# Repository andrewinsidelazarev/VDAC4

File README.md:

# VDAC4

Плата VDAC4 для ZX Evolution (TS-Config): Tang Nano 20K, модуль Waveshare
ESP32-S3-Zero-N8R8 и ЦАП PCM5102. ESP32-S3 подключена к Evo по SPI — к той же
шине, что и SD-карта (порты `#57`/`#77`), и работает ведомой: Z80 обращается к ней
двоичным протоколом ZiFi. Сеть, разбор HTTP, файловые серверы и декодирование
звука делает ESP; программы Z80 — плагины Wild Commander и `zifi.spg` —
показывают интерфейс и работают с картой Evo.

## Первая прошивка платы — готовая программа

> [!TIP]
> **Прошить новую плату или поставить прошивки заново можно готовой программой — собирать ничего не нужно.**
>
> **[⬇ Скачать VDAC4Flasher.exe](https://github.com/andrewinsidelazarev/VDAC4/raw/main/Flasher/VDAC4Flasher.exe)** — одна программа для Windows 10/11.
>
> Она сама скачивает свежие прошивки отсюда, с GitHub, и по шагам записывает их по USB во все три части платы:
> модуль ESP32-S3 Zero, BL616 модуля Tang Nano 20K и flash ПЛИС Tang. Перед записью старые прошивки сохраняются
> в папку `Backup` рядом с программой. Python, ESP-IDF, Gowin и другие программы не нужны.

Как пользоваться:

1. Создайте пустую папку (например, `VDAC4` на рабочем столе) и скачайте в неё `VDAC4Flasher.exe`.
2. Выньте плату VDAC4 из ZX Evolution или выключите Evo. **Питание Evo и USB одновременно не включать.**
3. Запустите программу. Если Windows покажет «Windows защитила ваш компьютер» (у программы нет цифровой
   подписи), нажмите «Подробнее», затем «Выполнить в любом случае».
4. Дальше программа ведёт сама — на каждом шаге в окне написано, куда подключить кабель:
   - шаг 1 — USB к модулю ESP32-S3 Zero;
   - шаг 2 — USB к модулю Tang Nano 20K с нажатой кнопкой UPDATE;
   - шаг 3 — USB к Tang ещё раз, уже без кнопки.

Нужны USB-кабель с данными (зарядный без данных не подойдёт) и интернет. Подробнее —
[`Flasher/README.md`](Flasher/README.md). Дальнейшие обновления прошивок идут по сети, из Wild Commander.

## Что где

| Папка | Что там |
|---|---|
| [`Docs`](Docs) | блок-схема платы VDAC4 A4 ([PNG](Docs/TS_VDAC_A4-block-diagram.png), [SVG](Docs/TS_VDAC_A4-block-diagram.svg), [PDF](Docs/TS_VDAC_A4-block-diagram.pdf)) |
| [`Hardware`](Hardware) | плата VDAC4, ревизии A5 (текущая) и A4: проекты KiCad, комплекты для заказа на JLCPCB, PDF схем и BOM; перемычки ЦАП и меры предосторожности — в [`Hardware/README.md`](Hardware/README.md) |
| [`ESP32 S3 Zero N8R8/Docs`](ESP32%20S3%20Zero%20N8R8/Docs) | ESP32-S3: схемы подключения (SPI к IDE-40, звук GY-PCM5102, распиновка), описание прошивки, канала SPI, команд и наладки ([`VDAC4.md`](ESP32%20S3%20Zero%20N8R8/Docs/VDAC4.md)), протокол кадров ([`PROTOCOL.md`](ESP32%20S3%20Zero%20N8R8/Docs/PROTOCOL.md)) |
| [`ESP32 S3 Zero N8R8/Firmware`](ESP32%20S3%20Zero%20N8R8/Firmware) | прошивка ESP32-S3: канал SPI, Wi-Fi, серверы, вывод звука, загрузчик модулей |
| [`ESP32 S3 Zero N8R8/Network`](ESP32%20S3%20Zero%20N8R8/Network) | сетевые программы Z80: `zifi.spg`, плагины FTP, SMB, NTP, WC Update, заставки погоды, утилиты |
| [`ESP32 S3 Zero N8R8/Sound`](ESP32%20S3%20Zero%20N8R8/Sound) | VDAC4 Media Player: модули ESP (декодеры) и плагин |
| [`Tang Nano 20k/Docs`](Tang%20Nano%2020k/Docs) | Tang Nano 20K: кадровый буфер TS-Config → HDMI 720p50, LINK с ESP, настройки во flash Tang, обновление через ESP ([`a3-fpga-framebuffer.md`](Tang%20Nano%2020k/Docs/a3-fpga-framebuffer.md)); генлок-тракт ([`a3-fpga-video.md`](Tang%20Nano%2020k/Docs/a3-fpga-video.md)); распиновка ESP/Tang ([`a3-interface-pinmap.md`](Tang%20Nano%2020k/Docs/a3-interface-pinmap.md)) |
| [`Tang Nano 20k/Firmware`](Tang%20Nano%2020k/Firmware) | прошивка Tang (GW2AR-18): RTL, тестбенчи, сборка в Gowin; готовые ядра flash Tang — TS-Config [`firmware/ts_fb_hdmi_top.fs`](Tang%20Nano%2020k/Firmware/firmware/ts_fb_hdmi_top.fs) (слот 0) и FT812 [`firmware/ts_fb_slot1.fs`](Tang%20Nano%2020k/Firmware/firmware/ts_fb_slot1.fs) (слот 1) |
| [`Tang Nano 20k/BL616`](Tang%20Nano%2020k/BL616) | прошивка BL616 модуля Tang: сопроцессор FT812, 3D-команды VDAC4, кэш ядер карты Tang, обновление по сети; готовый образ — прошивка 24 [`firmware/vdac4_copro_bl616.bin`](Tang%20Nano%2020k/BL616/firmware/vdac4_copro_bl616.bin) |
| [`Tang Nano 20k/FTVIEW4`](Tang%20Nano%2020k/FTVIEW4) | плагин Wild Commander FTVIEW4 для VDAC4: картинки и ролики через FT812 и BL616, MJPEG AVI — через ядро видео Tang (слот 3) и VIDEO.ELF на ESP; сборка — [`build/FTVIEW4.WMF`](Tang%20Nano%2020k/FTVIEW4/build/FTVIEW4.WMF) |
| [`Flasher`](Flasher) | первая прошивка платы по USB: программа для Windows [`VDAC4Flasher.exe`](Flasher/VDAC4Flasher.exe) шьёт ESP32-S3, BL616 и flash ПЛИС Tang прошивками с GitHub, перед записью сохраняя прежние в `Backup` |
| [`TS-Config`](TS-Config) | прошивка самой Evo: TS-Config для VDAC2 с SPI 28 МГц, с которой проверялась плата ([`zxevo_fw_vdac2-spi28.bin`](TS-Config/zxevo_fw_vdac2-spi28.bin), ставится как `ZXEVO_FW.BIN` с SD) |
| [`Tang Nano 20k/Cores`](Tang%20Nano%2020k/Cores) | все ядра Tang и их установка; ядра для карты Tang — ZX Spectrum Next и NES / Денди со слоями ESP, их исходники (GPL-3.0) и правка ROM NextZXOS |

Что нужно на стороне Evo — в
[README сетевой части](ESP32%20S3%20Zero%20N8R8/Network/README.md#что-нужно).

Собственный код — [MIT](LICENSE); сторонние компоненты и их лицензии перечислены
в README частей.

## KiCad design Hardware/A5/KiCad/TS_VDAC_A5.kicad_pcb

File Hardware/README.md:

# Плата VDAC4

Плата-носитель VDAC4 для ZX Evolution (TS-Config): 58×75 мм, 4 слоя. Сверху на гнёздах стоят
Tang Nano 20K (A1), Waveshare ESP32-S3-Zero-N8R8 (A2) и модуль ЦАП GY-PCM5102 (A3); снизу —
гнездо IDE-40 (J1), которым плата надевается прямо на разъём IDE Evo. Питание — от кабеля
питания дисковода (J5). Блок-схема — в [`Docs`](../Docs).

## Ревизии

| Ревизия | Что | Папка |
|---|---|---|
| **A5** (2026-10-24) — текущая | A4 без деталей Texas Instruments в U8, U11 и U10: U8/U11 — 74AHCT1G126GV (MDD, SOT-23-5, питание +5 В) вместо TXU0101, U10 — ME6211C33M5G-N (Microne) вместо TLV75533. Журнал — [`CHANGES_A5.md`](A5/KiCad/CHANGES_A5.md) | [`A5`](A5) |
| A4 (2026-10-20) | питание J5, перемычки ЦАП, выбор громкости, гнёзда под ЦАП, NT1 под провод, край экрана ЦАП, шелкография. Журнал — [`CHANGES_A4.md`](A4/KiCad/CHANGES_A4.md) | [`A4`](A4) |

Внутри папки ревизии:

| Папка | Что там |
|---|---|
| `Docs` | PDF: электрическая схема (4 листа), монтажная схема верха и низа, перечень элементов — [A5](A5/Docs), [A4](A4/Docs) |
| `KiCad` | проект KiCad 10: схема (4 листа), плата, библиотека проекта, правила DRC, журнал изменений — [A5](A5/KiCad), [A4](A4/KiCad) |
| `Production` | комплект для JLCPCB: Gerber и сверловка (`TS_VDAC_A5-A5-gerber.zip` / `TS_VDAC_A4-A4-gerber.zip`), `JLCPCB_BOM.csv`, `JLCPCB_CPL.csv`, отчёты DRC/ERC, `manifest.json` с SHA-256 файлов и параметрами выгрузки — [A5](A5/Production), [A4](A4/Production) |

Всё, что ниже, относится к обеим ревизиям: разводка платы, перемычки и разъёмы у них одинаковые.

## Осторожно

**Установка в IDE-40.** На некоторых версиях ZX Evolution на вывод-ключ IDE-40 (вывод 20)
заведено питание +5 В. На VDAC4 вывод J1.20 ни к чему не подключён, поэтому при правильной
установке это безопасно. Но если надеть плату со сдвигом на один вывод или ряд либо развернуть
её, +5 В попадёт на сигнальную линию или на землю — пострадают буферы платы, модули, а то и Evo.
Ставить плату только при выключенном питании, вывод 1 J1 — к выводу 1 разъёма Evo; перед
включением проверить, что все 40 выводов вошли в гнездо ровно.

**USB-C модулей.** Не подключать кабели USB-C к Tang Nano 20K и ESP32-S3-Zero при включённом
питании ZX Evolution. Прошивать модули по USB — с выключенной Evo или вынув плату из неё.

**Кабель питания +12 В.** Плате нужно только +5 В (J5, вывод 4, красный провод разъёма
дисковода); вывод 1 с +12 В (жёлтый провод) на плате ни к чему не подключён. Гораздо безопаснее
разомкнуть цепь +12 В в самом кабеле, который идёт к плате: тогда ни ошибка в кабеле, ни
неправильно надетый разъём не подадут 12 В на дорогостоящие сборки вроде Tang Nano 20K.

**Перемычка J1 на ZX Evolution должна быть замкнута.** Через неё идёт вывод 1 IDE-40, по
которому на плату приходит выбор ESP32 (`ESP_CS_N`); при разомкнутой J1 ESP со стороны Evo
не откликается.

**Перед первым включением** собранной платы — без модулей Tang, ESP и GY: вставить вилку питания
по ключу и убедиться, что между J5.4 и GND +5 В.

## Перемычки модуля ЦАП JP1–JP4

Четыре открытые паяльные перемычки снизу, под модулем ЦАП, задают выводы настройки
GY-PCM5102. С завода разомкнуты, замыкаются каплей припоя.

| Перемычка | Надпись на плате | Замкнутая соединяет | Что задаёт |
|---|---|---|---|
| JP1 | `FMT=L` | FMT → A_GND | формат I2S |
| JP2 | `XSMT=H` | XSMT → 3,3 В модуля | звук включён |
| JP3 | `DEMP=L` | DEMP → A_GND | коррекция (de-emphasis) выключена |
| JP4 | `FLT=L` | FLT → A_GND | обычный фильтр |

Рабочая настройка — замкнуть все четыре. У самого модуля GY-PCM5102 есть свои площадки H/L для
тех же выводов: уровень задаётся в одном месте — или на плате, или на модуле. **Нельзя** ставить
перемычку на плате и перемычку на модуле в противоположные стороны: это замыкание 3,3 В модуля
на землю.

## Громкость звука JP5, JP6

В каждом канале ЦАП на вход Evo всегда стоит 27 кОм (R17, R18). Трёхконтактные перемычки JP5
(левый канал) и JP6 (правый) снизу у разъёма J2 подключают параллельно ещё один резистор.

| Перемычка | Сопротивление | Размах на выходе Evo | Громче, чем без перемычки |
|---|---|---|---|
| не замкнута | 27k | 1,37 В | 0 дБ |
| середина — «15k» | 27k ∥ 34k = 15,05k | 2,06 В | +3,5 дБ |
| середина — «9k1» | 27k ∥ 13,7k = 9,09k | 2,75 В | +6,0 дБ |

Оба канала замыкать одинаково. Все три площадки сразу не замыкать: вместе с AY звук выйдет за
неискажённый размах микшера Evo. Расчёт — в [`CHANGES_A4.md`](A4/KiCad/CHANGES_A4.md), раздел 3.

## NT1 — связь аналоговой и цифровой земли

NT1 — единственное место, где земля звука (A_GND) соединяется с общей землёй платы. Медные
перемычки между её площадками есть сверху и снизу; площадки 2 мм с отверстиями 1 мм оставлены
под дополнительный провод, если металлизация окажется плохой. NT1 стоит под модулем ЦАП, правее
перемычек JP1–JP4 (надпись `AGND-GND`).

Заливки земли под модулем ЦАП заканчиваются на 2,54 мм выше его ряда цифровых выводов; от этой
линии до ESP32 на всех слоях земли нет, чтобы меньше экранировать антенну Wi-Fi.

## Заказ на JLCPCB

- **Плата:** 4 слоя, 1,6 мм, FR-4, внешняя медь 1 oz, внутренняя 0,5 oz, переходные закрыты
  (Plugged), HASL. Цвет любой.
- **Сборка:** Standard PCBA, обе стороны, технологические поля добавляет JLCPCB (плата меньше
  70×70 мм). «Confirm Parts Placement» стоит включить.
- **Файлы** из `Production` нужной ревизии: Gerber-архив — на шаге платы; `JLCPCB_BOM.csv` и
  `JLCPCB_CPL.csv` — на шаге сборки. Все 24 типа деталей сопоставляются с LCSC автоматически
  (октябрь 2026).
- **A5: проверить U10 в просмотрщике JLCPCB.** У ME6211 посадка в библиотеке JLCPCB нарисована
  иначе, чем у прежнего TLV75533; угол в CPL оставлен 90°. Метка вывода 1 U10 должна лечь на ключ
  шелкографии, иначе нужен угол 0° или 180°.
- Фабрика ставит SMD снизу и выводные разъёмы и гнёзда (J1, J2, J5, J6–J11). Модули Tang, ESP
  и GY-PCM5102 вставляет пользователь. Перемычки JP1–JP6 и провод в NT1 фабрика не запаивает.
- Ориентир для A4 (октябрь 2026): 5 плат и сборка 2 из них — около 127 € без доставки и налогов.

## Проверки

ERC — 0 нарушений. DRC — 0 неподключённых, 0 расхождений со схемой; два замечания «PTH внутри
посадочного места A3» (NT1 под модулем ЦАП, который стоит на гнёздах высотой 8,5 мм) внесены
в исключения проекта с комментарием.

3D-модели Tang Nano 20K и ESP32-S3-Zero в комплект не входят (модели производителей): KiCad ищет
их по пути `../../../docs/references/3d-models-20260908/` от папки проекта. Остальные модели — из
стандартной библиотеки KiCad и из `KiCad/Libraries/3D`.

У A5 в `Production/manifest.json` перечислены и PDF из `Docs` — их SHA-256 тоже там.

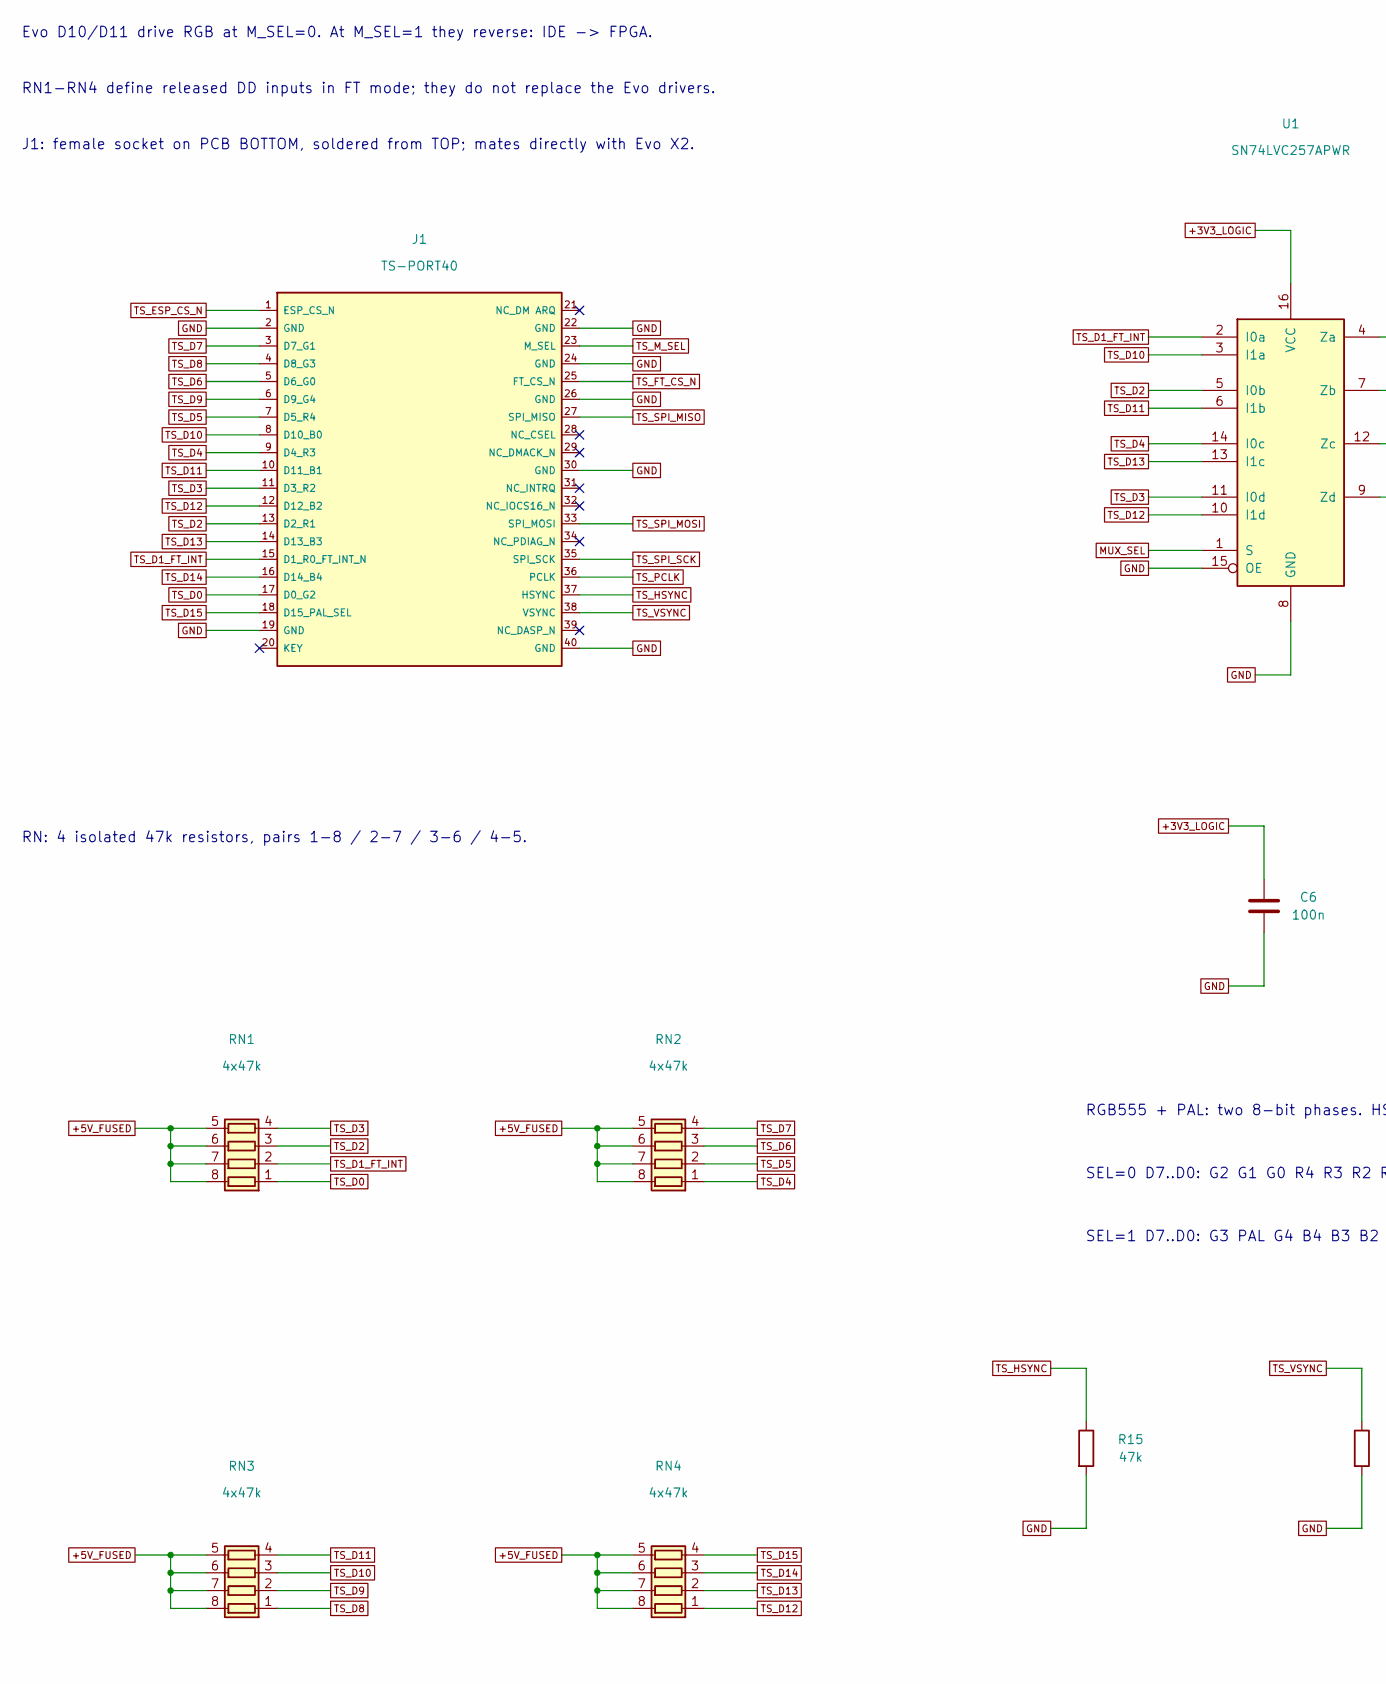
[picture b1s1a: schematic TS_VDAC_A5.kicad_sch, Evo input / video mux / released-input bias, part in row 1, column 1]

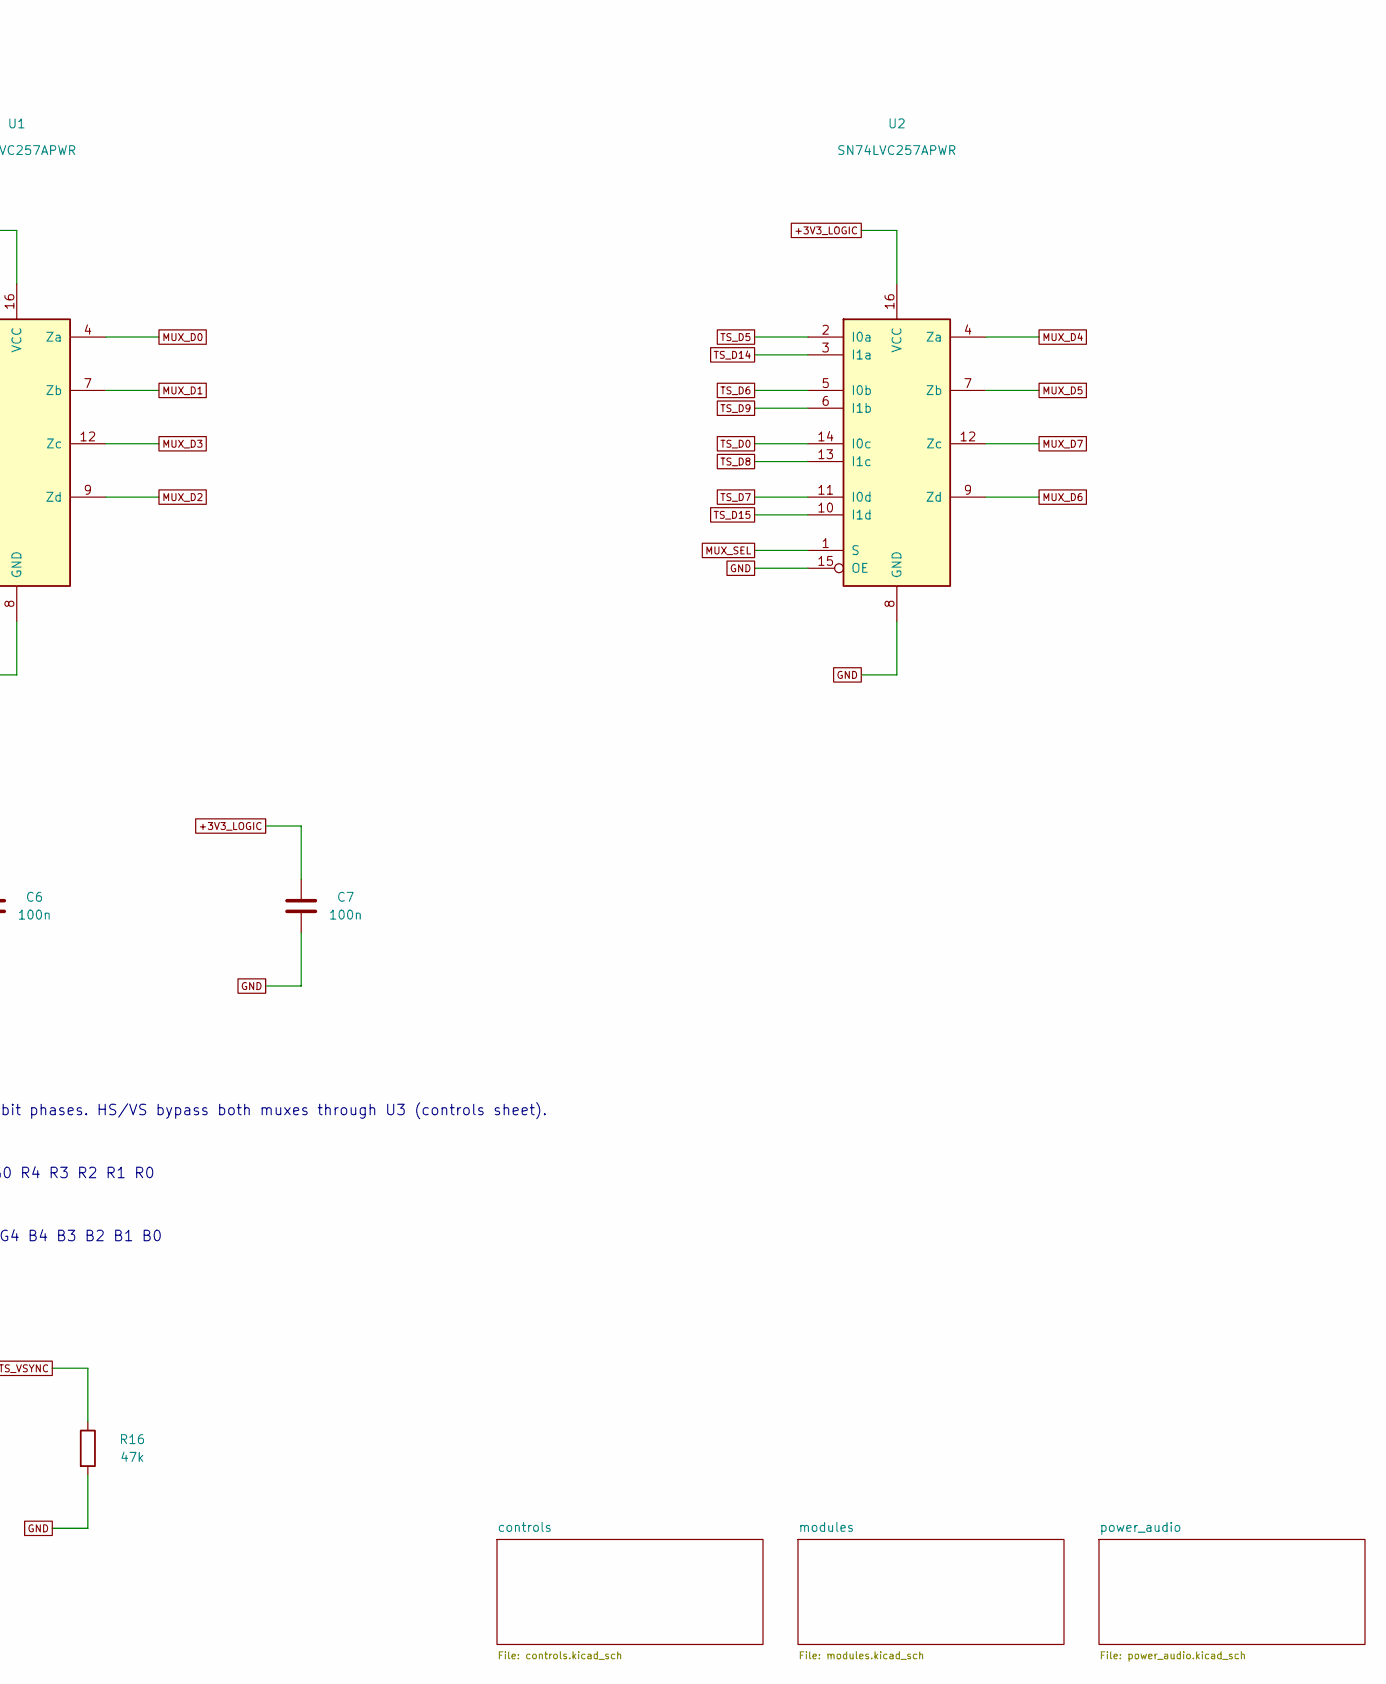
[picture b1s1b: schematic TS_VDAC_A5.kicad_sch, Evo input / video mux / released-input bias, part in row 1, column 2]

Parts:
C6, C7: 100n; C_0805_2012Metric; MPN CC0805KRX7R9BB104; LCSC C49678
J1: TS-PORT40; PinSocket_2x20_P2.54mm_Vertical; MPN 2.54-2*20; LCSC C2977589
R15, R16: 47k; R_0805_2012Metric; MPN 0805W8F4702T5E; LCSC C17713
RN1, RN2, RN3, RN4: 4x47k; R_Array_Convex_4x0603; MPN YC164-JR-0747KL; LCSC C779384
U1, U2: SN74LVC257APWR; TSSOP-16_4.4x5mm_P0.65mm; MPN SN74LVC257APWR; LCSC C205921

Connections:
+3V3_LOGIC: C6.1, C7.1, U1.16 (VCC), U2.16 (VCC); also elsewhere on the board
+5V_FUSED: RN1.5 (R4.2), RN1.6 (R3.2), RN1.7 (R2.2), RN1.8 (R1.2), RN2.5 (R4.2), RN2.6 (R3.2), RN2.7 (R2.2), RN2.8 (R1.2), RN3.5 (R4.2), RN3.6 (R3.2), RN3.7 (R2.2), RN3.8 (R1.2), RN4.5 (R4.2), RN4.6 (R3.2), RN4.7 (R2.2), RN4.8 (R1.2); also elsewhere on the board
GND: C6.2, C7.2, J1.2 (GND), J1.19 (GND), J1.22 (GND), J1.24 (GND), J1.26 (GND), J1.30 (GND), J1.40 (GND), R15.2, R16.2, U1.8 (GND), U1.15 (OE), U2.8 (GND), U2.15 (OE); also elsewhere on the board
MUX_D0: U1.4 (Za); also elsewhere on the board
MUX_D1: U1.7 (Zb); also elsewhere on the board
MUX_D2: U1.9 (Zd); also elsewhere on the board
MUX_D3: U1.12 (Zc); also elsewhere on the board
MUX_D4: U2.4 (Za); also elsewhere on the board
MUX_D5: U2.7 (Zb); also elsewhere on the board
MUX_D6: U2.9 (Zd); also elsewhere on the board
MUX_D7: U2.12 (Zc); also elsewhere on the board
MUX_SEL: U1.1 (S), U2.1 (S); also elsewhere on the board
TS_D0: J1.17 (D0_G2), RN1.1 (R1.1), U2.14 (I0c)
TS_D1_FT_INT: J1.15 (D1_R0_FT_INT_N), RN1.2 (R2.1), U1.2 (I0a); also elsewhere on the board
TS_D2: J1.13 (D2_R1), RN1.3 (R3.1), U1.5 (I0b)
TS_D3: J1.11 (D3_R2), RN1.4 (R4.1), U1.11 (I0d)
TS_D4: J1.9 (D4_R3), RN2.1 (R1.1), U1.14 (I0c)
TS_D5: J1.7 (D5_R4), RN2.2 (R2.1), U2.2 (I0a)
TS_D6: J1.5 (D6_G0), RN2.3 (R3.1), U2.5 (I0b)
TS_D7: J1.3 (D7_G1), RN2.4 (R4.1), U2.11 (I0d)
TS_D8: J1.4 (D8_G3), RN3.1 (R1.1), U2.13 (I1c)
TS_D9: J1.6 (D9_G4), RN3.2 (R2.1), U2.6 (I1b)
TS_D10: J1.8 (D10_B0), RN3.3 (R3.1), U1.3 (I1a)
TS_D11: J1.10 (D11_B1), RN3.4 (R4.1), U1.6 (I1b)
TS_D12: J1.12 (D12_B2), RN4.1 (R1.1), U1.10 (I1d)
TS_D13: J1.14 (D13_B3), RN4.2 (R2.1), U1.13 (I1c)
TS_D14: J1.16 (D14_B4), RN4.3 (R3.1), U2.3 (I1a)
TS_D15: J1.18 (D15_PAL_SEL), RN4.4 (R4.1), U2.10 (I1d)
TS_ESP_CS_N: J1.1 (ESP_CS_N); also elsewhere on the board
TS_FT_CS_N: J1.25 (FT_CS_N); also elsewhere on the board
TS_HSYNC: J1.37 (HSYNC), R15.1; also elsewhere on the board
TS_M_SEL: J1.23 (M_SEL); also elsewhere on the board
TS_PCLK: J1.36 (PCLK); also elsewhere on the board
TS_SPI_MISO: J1.27 (SPI_MISO); also elsewhere on the board
TS_SPI_MOSI: J1.33 (SPI_MOSI); also elsewhere on the board
TS_SPI_SCK: J1.35 (SPI_SCK); also elsewhere on the board
TS_VSYNC: J1.38 (VSYNC), R16.1; also elsewhere on the board

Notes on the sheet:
Evo D10/D11 drive RGB at M_SEL=0. At M_SEL=1 they reverse: IDE -> FPGA.
RN1-RN4 define released DD inputs in FT mode; they do not replace the Evo drivers.
J1: female socket on PCB BOTTOM, soldered from TOP; mates directly with Evo X2.
RN: 4 isolated 47k resistors, pairs 1-8 / 2-7 / 3-6 / 4-5.
RGB555 + PAL: two 8-bit phases. HS/VS bypass both muxes through U3 (controls sheet).
SEL=0 D7..D0: G2 G1 G0 R4 R3 R2 R1 R0
SEL=1 D7..D0: G3 PAL G4 B4 B3 B2 B1 B0

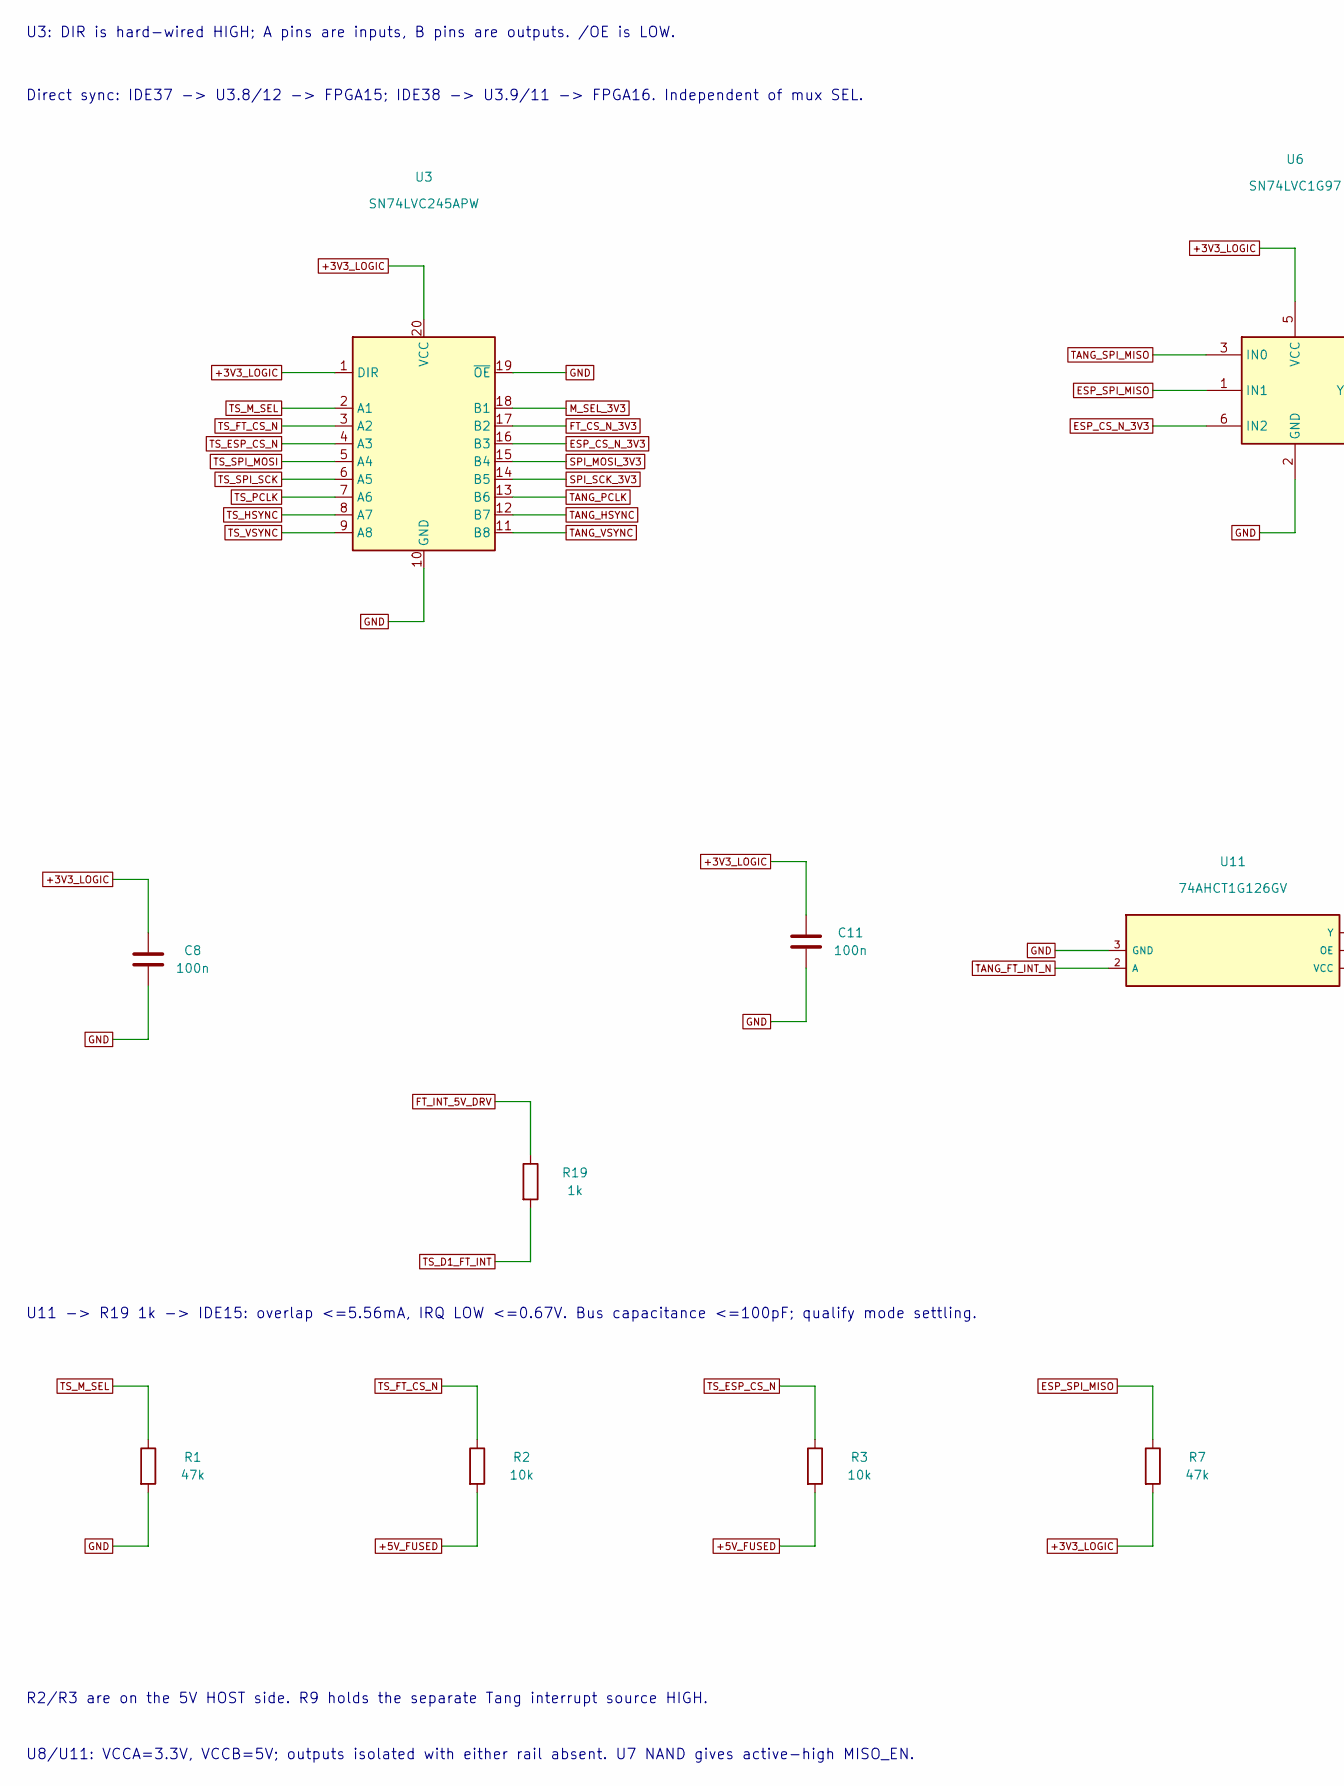
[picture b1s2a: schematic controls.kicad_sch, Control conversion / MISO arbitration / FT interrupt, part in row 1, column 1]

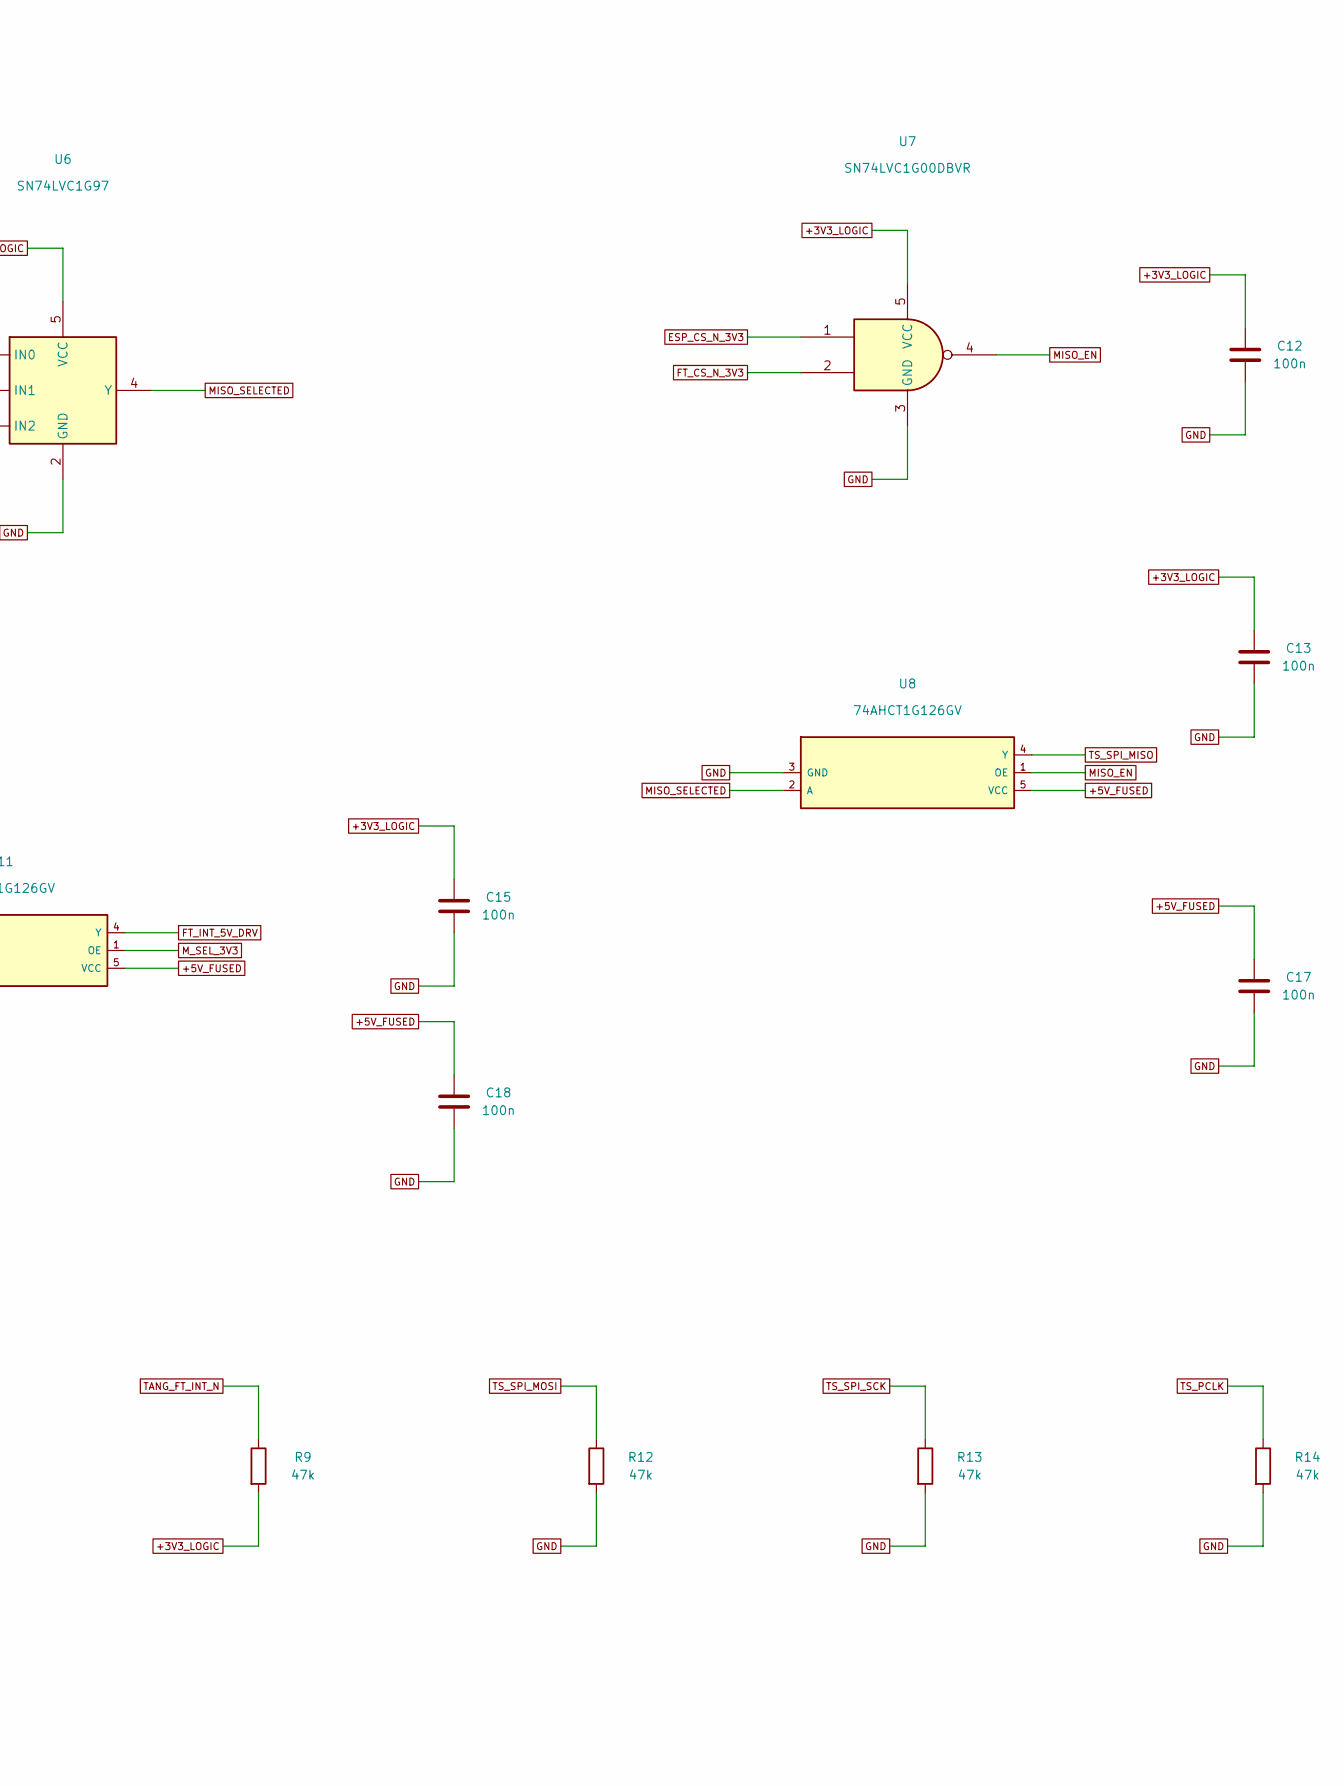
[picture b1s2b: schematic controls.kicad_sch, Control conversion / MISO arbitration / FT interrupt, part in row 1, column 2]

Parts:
C8, C11, C12, C13, C15, C17, C18: 100n; C_0805_2012Metric; MPN CC0805KRX7R9BB104; LCSC C49678
R1, R7, R9, R12, R13, R14: 47k; R_0805_2012Metric; MPN 0805W8F4702T5E; LCSC C17713
R2, R3: 10k; R_0805_2012Metric; MPN 0805W8F1002T5E; LCSC C17414
R19: 1k; R_0805_2012Metric; MPN 0805W8F1001T5E; LCSC C17513
U3: SN74LVC245APW; TSSOP-20_4.4x6.5mm_P0.65mm; MPN SN74LVC245APWR; LCSC C7848
U6: SN74LVC1G97; SOT-23-6; MPN SN74LVC1G97DBVR; LCSC C128411
U7: SN74LVC1G00DBVR; SOT-23-5; MPN SN74LVC1G00DBVR; LCSC C7826
U8, U11: 74AHCT1G126GV; SOT-23-5; MPN 74AHCT1G126GV; LCSC C52140416

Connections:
+3V3_LOGIC: C8.1, C11.1, C12.1, C13.1, C15.1, R7.2, R9.2, U3.1 (DIR), U3.20 (VCC), U6.5 (VCC), U7.5 (VCC); also elsewhere on the board
+5V_FUSED: C17.1, C18.1, R2.2, R3.2, U8.5 (VCC), U11.5 (VCC); also elsewhere on the board
ESP_CS_N_3V3: U3.16 (B3), U6.6 (IN2), U7.1; also elsewhere on the board
ESP_SPI_MISO: R7.1, U6.1 (IN1); also elsewhere on the board
FT_CS_N_3V3: U3.17 (B2), U7.2; also elsewhere on the board
FT_INT_5V_DRV: R19.1, U11.4 (Y)
GND: C8.2, C11.2, C12.2, C13.2, C15.2, C17.2, C18.2, R1.2, R12.2, R13.2, R14.2, U3.10 (GND), U3.19 (~OE), U6.2 (GND), U7.3 (GND), U8.3 (GND), U11.3 (GND); also elsewhere on the board
MISO_EN: U7.4, U8.1 (OE)
MISO_SELECTED: U6.4 (Y), U8.2 (A)
M_SEL_3V3: U3.18 (B1), U11.1 (OE); also elsewhere on the board
SPI_MOSI_3V3: U3.15 (B4); also elsewhere on the board
SPI_SCK_3V3: U3.14 (B5); also elsewhere on the board
TANG_FT_INT_N: R9.1, U11.2 (A); also elsewhere on the board
TANG_HSYNC: U3.12 (B7); also elsewhere on the board
TANG_PCLK: U3.13 (B6); also elsewhere on the board
TANG_SPI_MISO: U6.3 (IN0); also elsewhere on the board
TANG_VSYNC: U3.11 (B8); also elsewhere on the board
TS_D1_FT_INT: R19.2; also elsewhere on the board
TS_ESP_CS_N: R3.1, U3.4 (A3); also elsewhere on the board
TS_FT_CS_N: R2.1, U3.3 (A2); also elsewhere on the board
TS_HSYNC: U3.8 (A7); also elsewhere on the board
TS_M_SEL: R1.1, U3.2 (A1); also elsewhere on the board
TS_PCLK: R14.1, U3.7 (A6); also elsewhere on the board
TS_SPI_MISO: U8.4 (Y); also elsewhere on the board
TS_SPI_MOSI: R12.1, U3.5 (A4); also elsewhere on the board
TS_SPI_SCK: R13.1, U3.6 (A5); also elsewhere on the board
TS_VSYNC: U3.9 (A8); also elsewhere on the board

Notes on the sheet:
U3: DIR is hard-wired HIGH; A pins are inputs, B pins are outputs. /OE is LOW.
Direct sync: IDE37 -> U3.8/12 -> FPGA15; IDE38 -> U3.9/11 -> FPGA16. Independent of mux SEL.
U8/U11: VCCA=3.3V, VCCB=5V; outputs isolated with either rail absent. U7 NAND gives active-high MISO_EN.
U11 -> R19 1k -> IDE15: overlap <=5.56mA, IRQ LOW <=0.67V. Bus capacitance <=100pF; qualify mode settling.
R2/R3 are on the 5V HOST side. R9 holds the separate Tang interrupt source HIGH.

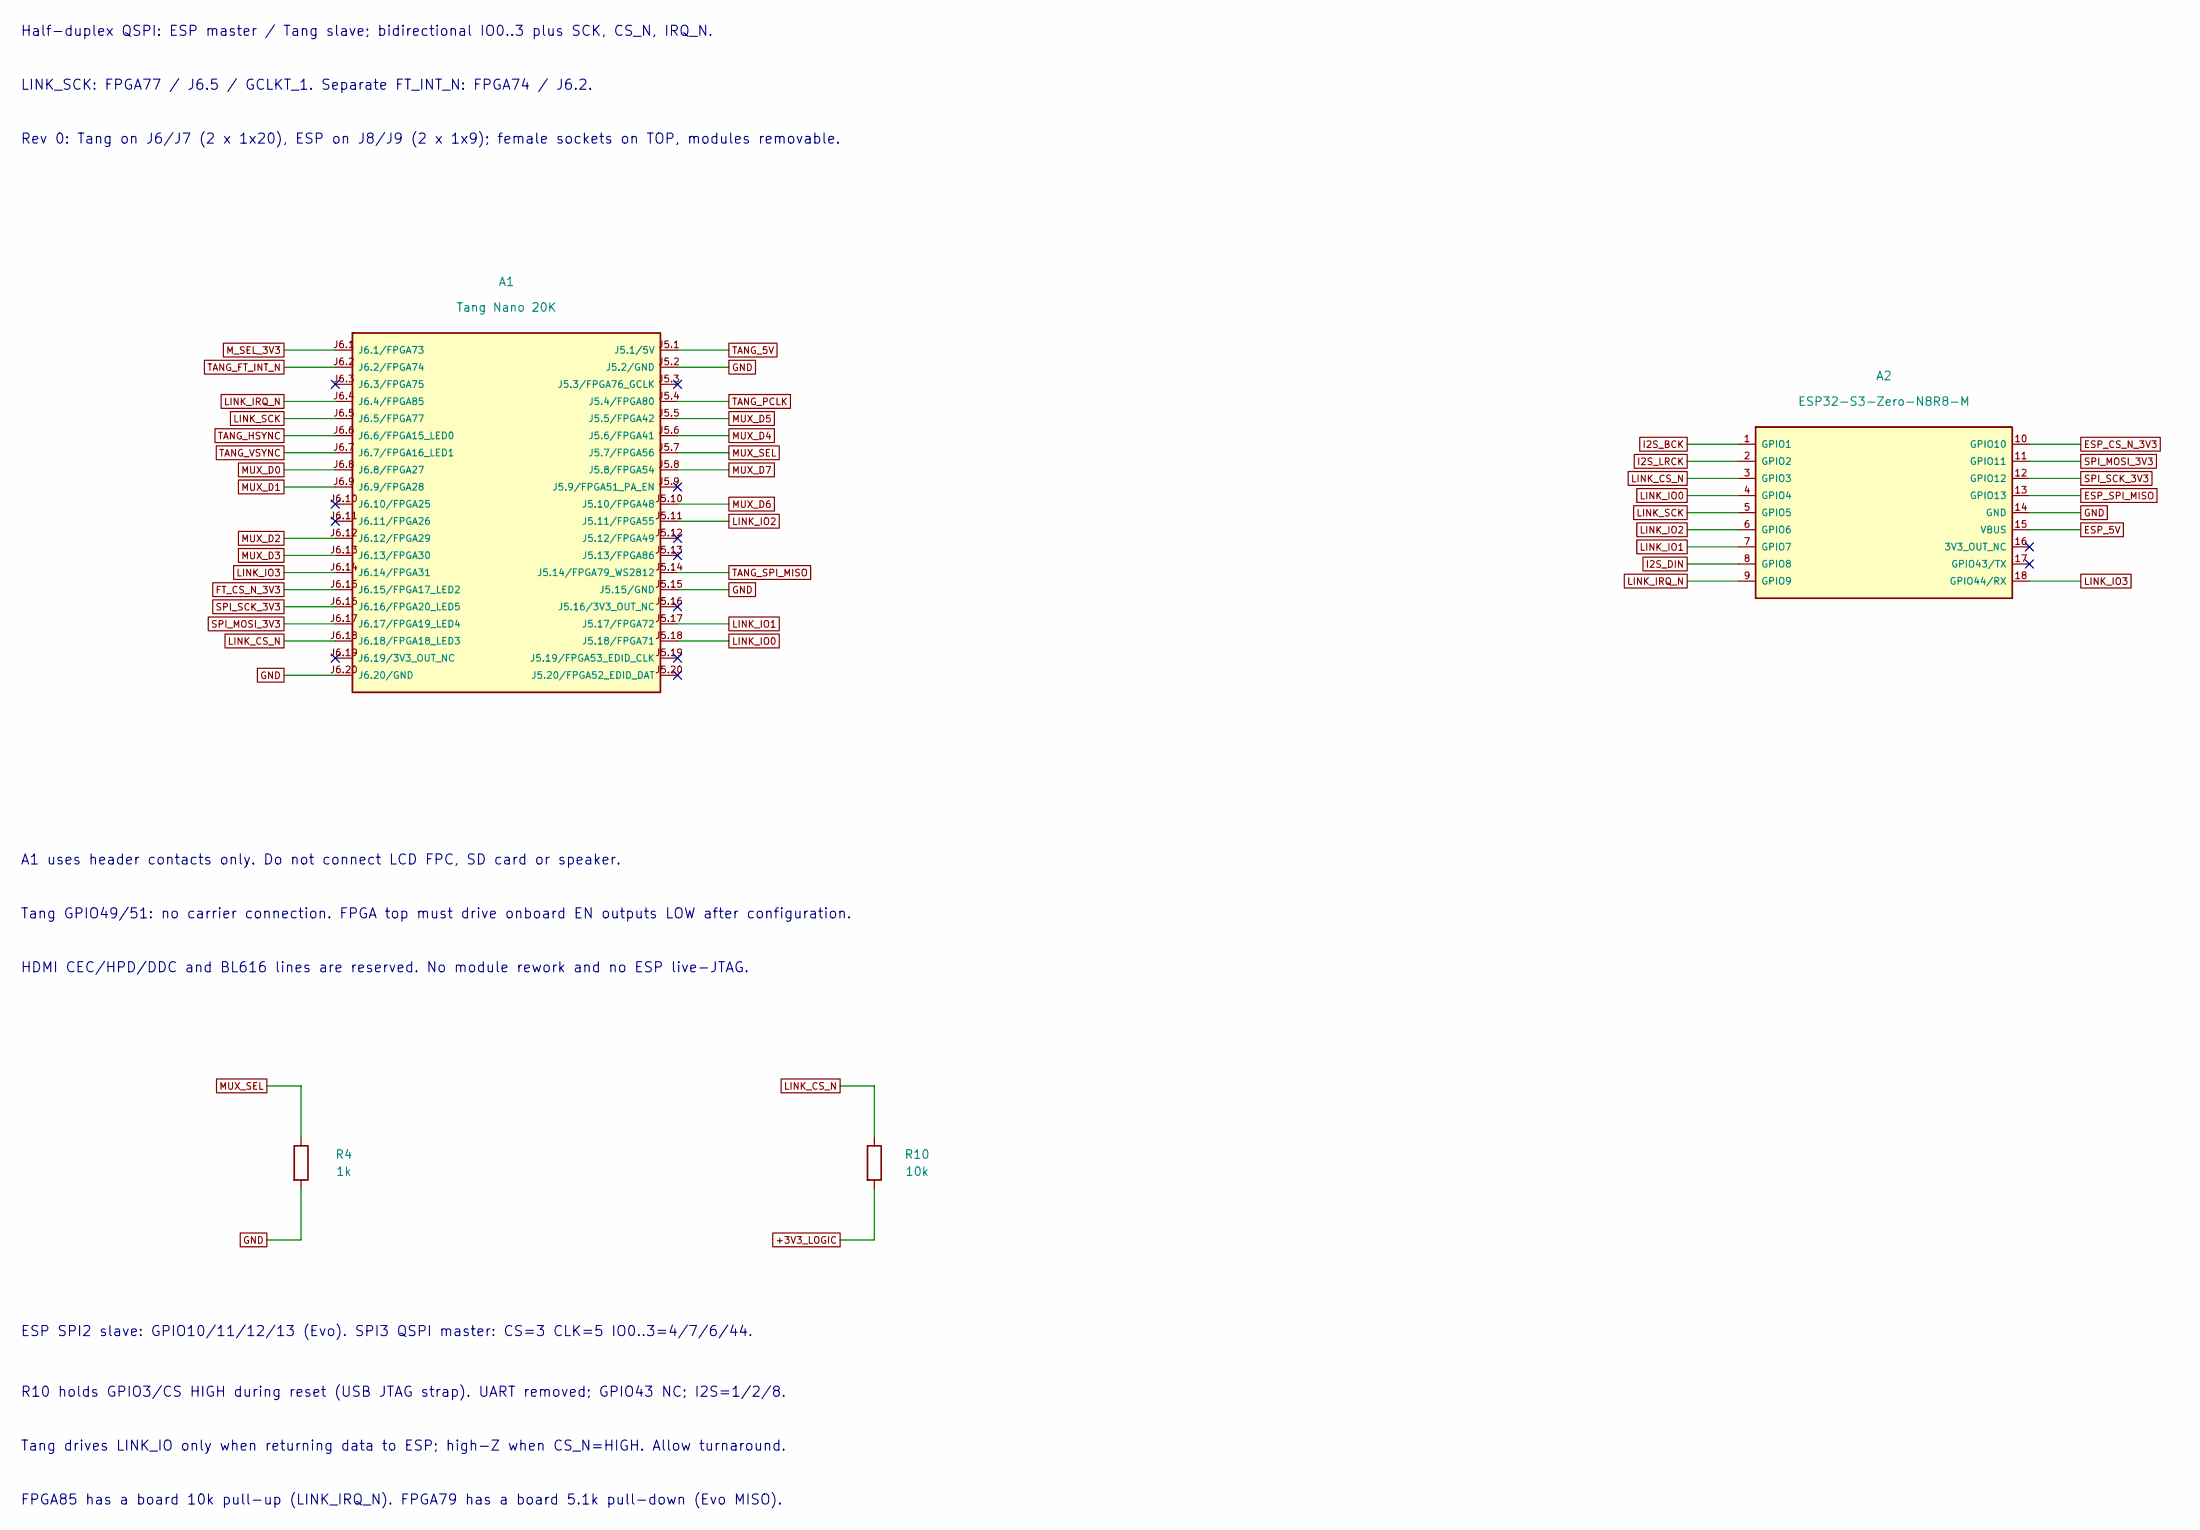
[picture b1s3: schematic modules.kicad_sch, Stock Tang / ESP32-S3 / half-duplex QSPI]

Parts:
A1: Tang Nano 20K; Tang_Nano_20K_2x1x20_P2.54mm; MPN Tang Nano 20K
A2: ESP32-S3-Zero-N8R8-M; ESP32-S3-Zero_2x1x09_P2.54mm; MPN ESP32-S3-Zero-N8R8-M
R4: 1k; R_0805_2012Metric; MPN 0805W8F1001T5E; LCSC C17513
R10: 10k; R_0805_2012Metric; MPN 0805W8F1002T5E; LCSC C17414

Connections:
+3V3_LOGIC: R10.2; also elsewhere on the board
ESP_5V: A2.15 (VBUS); also elsewhere on the board
ESP_CS_N_3V3: A2.10 (GPIO10); also elsewhere on the board
ESP_SPI_MISO: A2.13 (GPIO13); also elsewhere on the board
FT_CS_N_3V3: A1.J6.15 (J6.15/FPGA17_LED2); also elsewhere on the board
GND: A1.J5.2 (J5.2/GND), A1.J5.15 (J5.15/GND), A1.J6.20 (J6.20/GND), A2.14 (GND), R4.2; also elsewhere on the board
I2S_BCK: A2.1 (GPIO1); also elsewhere on the board
I2S_DIN: A2.8 (GPIO8); also elsewhere on the board
I2S_LRCK: A2.2 (GPIO2); also elsewhere on the board
LINK_CS_N: A1.J6.18 (J6.18/FPGA18_LED3), A2.3 (GPIO3), R10.1
LINK_IO0: A1.J5.18 (J5.18/FPGA71), A2.4 (GPIO4)
LINK_IO1: A1.J5.17 (J5.17/FPGA72), A2.7 (GPIO7)
LINK_IO2: A1.J5.11 (J5.11/FPGA55), A2.6 (GPIO6)
LINK_IO3: A1.J6.14 (J6.14/FPGA31), A2.18 (GPIO44/RX)
LINK_IRQ_N: A1.J6.4 (J6.4/FPGA85), A2.9 (GPIO9)
LINK_SCK: A1.J6.5 (J6.5/FPGA77), A2.5 (GPIO5)
MUX_D0: A1.J6.8 (J6.8/FPGA27); also elsewhere on the board
MUX_D1: A1.J6.9 (J6.9/FPGA28); also elsewhere on the board
MUX_D2: A1.J6.12 (J6.12/FPGA29); also elsewhere on the board
MUX_D3: A1.J6.13 (J6.13/FPGA30); also elsewhere on the board
MUX_D4: A1.J5.6 (J5.6/FPGA41); also elsewhere on the board
MUX_D5: A1.J5.5 (J5.5/FPGA42); also elsewhere on the board
MUX_D6: A1.J5.10 (J5.10/FPGA48); also elsewhere on the board
MUX_D7: A1.J5.8 (J5.8/FPGA54); also elsewhere on the board
MUX_SEL: A1.J5.7 (J5.7/FPGA56), R4.1; also elsewhere on the board
M_SEL_3V3: A1.J6.1 (J6.1/FPGA73); also elsewhere on the board
SPI_MOSI_3V3: A1.J6.17 (J6.17/FPGA19_LED4), A2.11 (GPIO11); also elsewhere on the board
SPI_SCK_3V3: A1.J6.16 (J6.16/FPGA20_LED5), A2.12 (GPIO12); also elsewhere on the board
TANG_5V: A1.J5.1 (J5.1/5V); also elsewhere on the board
TANG_FT_INT_N: A1.J6.2 (J6.2/FPGA74); also elsewhere on the board
TANG_HSYNC: A1.J6.6 (J6.6/FPGA15_LED0); also elsewhere on the board
TANG_PCLK: A1.J5.4 (J5.4/FPGA80); also elsewhere on the board
TANG_SPI_MISO: A1.J5.14 (J5.14/FPGA79_WS2812); also elsewhere on the board
TANG_VSYNC: A1.J6.7 (J6.7/FPGA16_LED1); also elsewhere on the board

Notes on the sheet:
Half-duplex QSPI: ESP master / Tang slave; bidirectional IO0..3 plus SCK, CS_N, IRQ_N.
LINK_SCK: FPGA77 / J6.5 / GCLKT_1. Separate FT_INT_N: FPGA74 / J6.2.
Rev 0: Tang on J6/J7 (2 x 1x20), ESP on J8/J9 (2 x 1x9); female sockets on TOP, modules removable.
A1 uses header contacts only. Do not connect LCD FPC, SD card or speaker.
Tang GPIO49/51: no carrier connection. FPGA top must drive onboard EN outputs LOW after configuration.
HDMI CEC/HPD/DDC and BL616 lines are reserved. No module rework and no ESP live-JTAG.
ESP SPI2 slave: GPIO10/11/12/13 (Evo). SPI3 QSPI master: CS=3 CLK=5 IO0..3=4/7/6/44.
R10 holds GPIO3/CS HIGH during reset (USB JTAG strap). UART removed; GPIO43 NC; I2S=1/2/8.
Tang drives LINK_IO only when returning data to ESP; high-Z when CS_N=HIGH. Allow turnaround.
FPGA85 has a board 10k pull-up (LINK_IRQ_N). FPGA79 has a board 5.1k pull-down (Evo MISO).

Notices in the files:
Hardware/A5/KiCad/TS_VDAC_A5.kicad_pcb:
VDAC4 HDMI - (C) 2026 INSiDE
